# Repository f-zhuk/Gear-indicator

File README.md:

# Gear-indicator
A system to monitor the selected gear for bicycles, for those who do not trust their memory

Headunit - a device to display the current gear
Gearunit - a device to transmit the current position of two cables, doubles as a power supply

### System manifest

The main idea of the system is to minimize interaction with the user, reduce buttons and/or settings to the minimum.

The system is designed for long-term/permanent installation and should require minimal maintenance. All its modules should be waterproof and vandal-resistant.

System retains its settings in the local RAM of the corresponding units, always powered from the Battery/shifter unit. If that battery goes flat, all system parameters are lost, and calibration (or learning) should be performed after turning on. Modules can be disconnected from power independently, so it will affect only the related module parameters. 

### Calibration

Whatever position the shifter was left in, it will be considered a first gear after the cold start. First shift has to be upwards, even an incomplete one, to point the cable’s forward direction. If the Headunit reads values outside of the known range, the current gear indicator will move away, and if the value stays stable for ~2 seconds, the gear count and associated shifter value table will be updated.

To save battery, all modules should go in and out of deep sleep upon Headunit's request. While active, deep sleep should be triggered if no movement is detected for a minute. 
While in a deep sleep, any movement should trigger a deep sleep exit.

With an IMU within the battery module firmly attached to the bicycle frame, it is possible to estimate bike speed.

Braking range can be determined and dynamically expanded on the fly.

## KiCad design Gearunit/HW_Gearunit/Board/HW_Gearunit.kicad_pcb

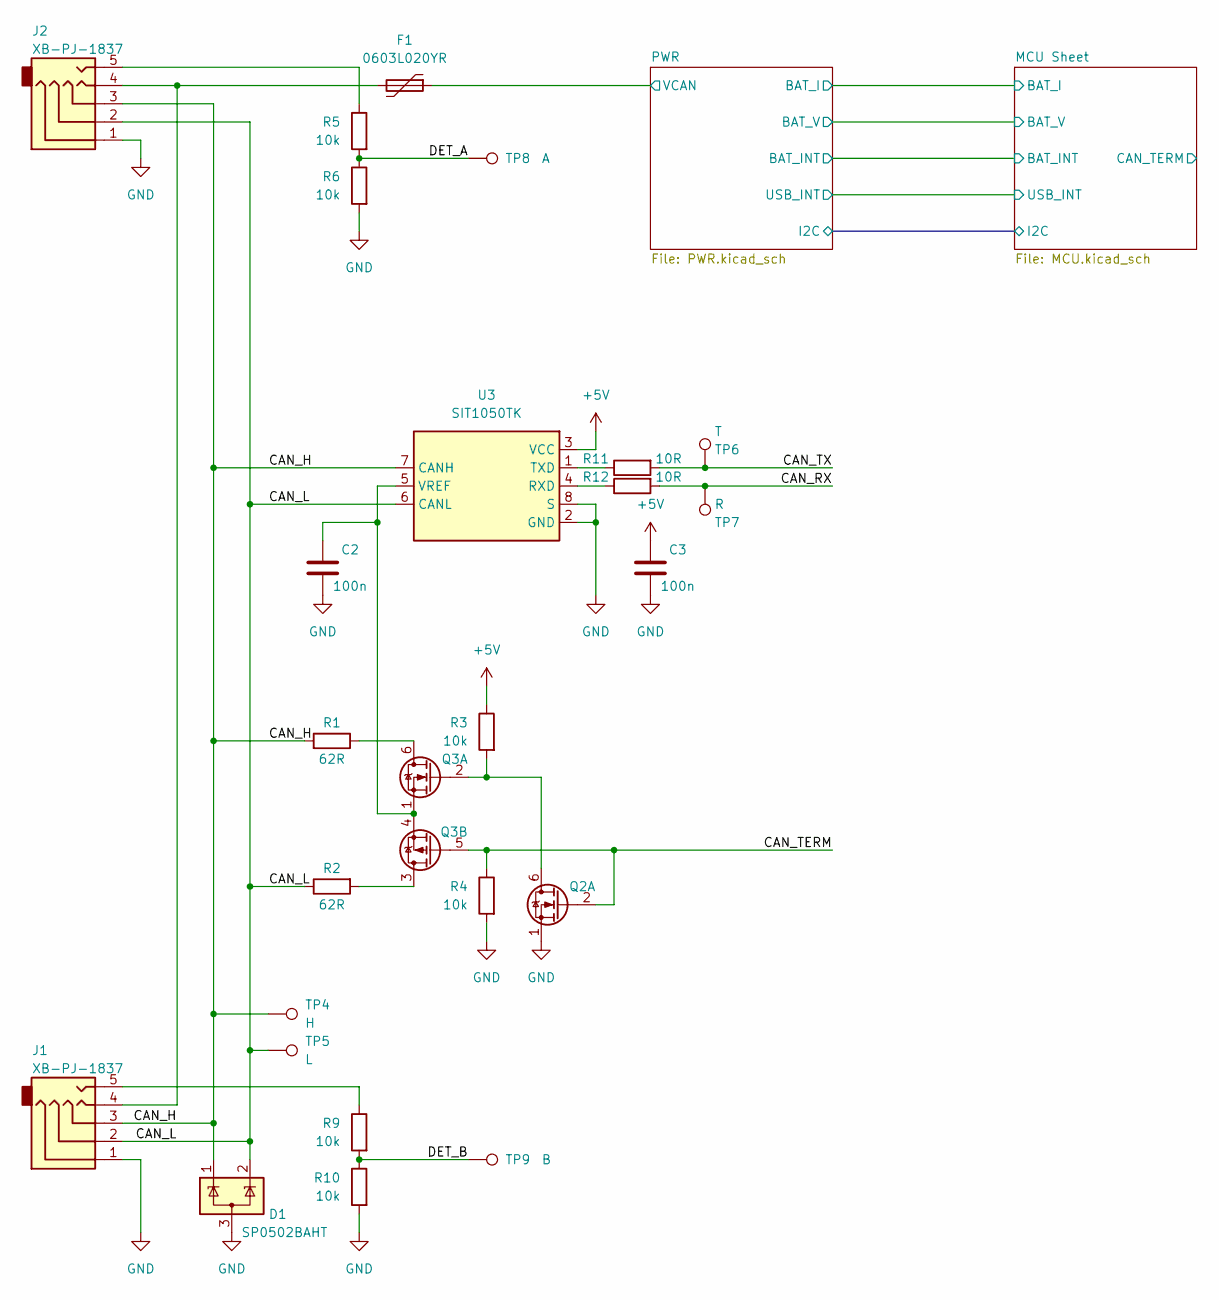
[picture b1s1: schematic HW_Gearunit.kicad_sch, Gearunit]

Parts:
C2, C3: 100n; C_0402_1005Metric; MPN CL05B104KB54PNC
D1: SP0502BAHT; SOT-23; MPN SP0502BAHT
F1: 0603L020YR; Fuse_0603_1608Metric; MPN 0603L020YR
J1, J2: XB-PJ-1837; MPN XB-PJ-1837
Q2, Q3: DMC2400UV; SOT-563; MPN DMC2400UV
R1, R2: 62R; R_0805_2012Metric; MPN RC0805FR-0762RL
R3, R4, R5, R6, R9, R10: 10k; R_0402_1005Metric; MPN 0402WGF1002TCE
R11, R12: 10R; R_0402_1005Metric; MPN 0402WGF100JTCE
TP4: H; TestPoint_Pad_D1.5mm
TP5: L; TestPoint_Pad_D1.5mm
TP6: T; TestPoint_Pad_D1.5mm
TP7: R; TestPoint_Pad_D1.5mm
TP8: A; TestPoint_Pad_D1.5mm
TP9: B; TestPoint_Pad_D1.5mm
U3: SIT1050TK; DFN-8-1EP_3x3mm_P0.65mm_EP1.5x2.25mm; MPN SIT1050TK

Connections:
+5V: C3.2, R3.1, U3.3 (VCC)
/CAN_H: D1.1 (K), J1.3, J2.3, R1.2, TP4.1, U3.7 (CANH)
/CAN_L: D1.2 (K), J1.2, J2.2, R2.1, TP5.1, U3.6 (CANL)
/CAN_RX: R12.2, TP7.1
/CAN_TERM: Q2.2 (G), Q3.5 (G), R4.1
/CAN_TX: R11.2, TP6.1
/DET_A: R5.2, R6.1, TP8.1
/DET_B: R9.2, R10.1, TP9.1
/PWR/VCAN: F1.1; also elsewhere on the board
GND: C2.1, C3.1, D1.3 (A), J1.1, J2.1, Q2.1 (S), R4.2, R6.2, R10.2, U3.2 (GND), U3.8 (S); also elsewhere on the board
unnamed: F1.2, J1.4, J2.4
unnamed: J1.5, R9.1
unnamed: J2.5, R5.1
unnamed: Q2.6 (D), Q3.2 (G), R3.2
unnamed: Q3.6 (D), R1.1
unnamed: C2.2, Q3.1 (S), Q3.4 (S), U3.5 (VREF)
unnamed: Q3.3 (D), R2.2
unnamed: R12.1, U3.4 (RXD)
unnamed: R11.1, U3.1 (TXD)

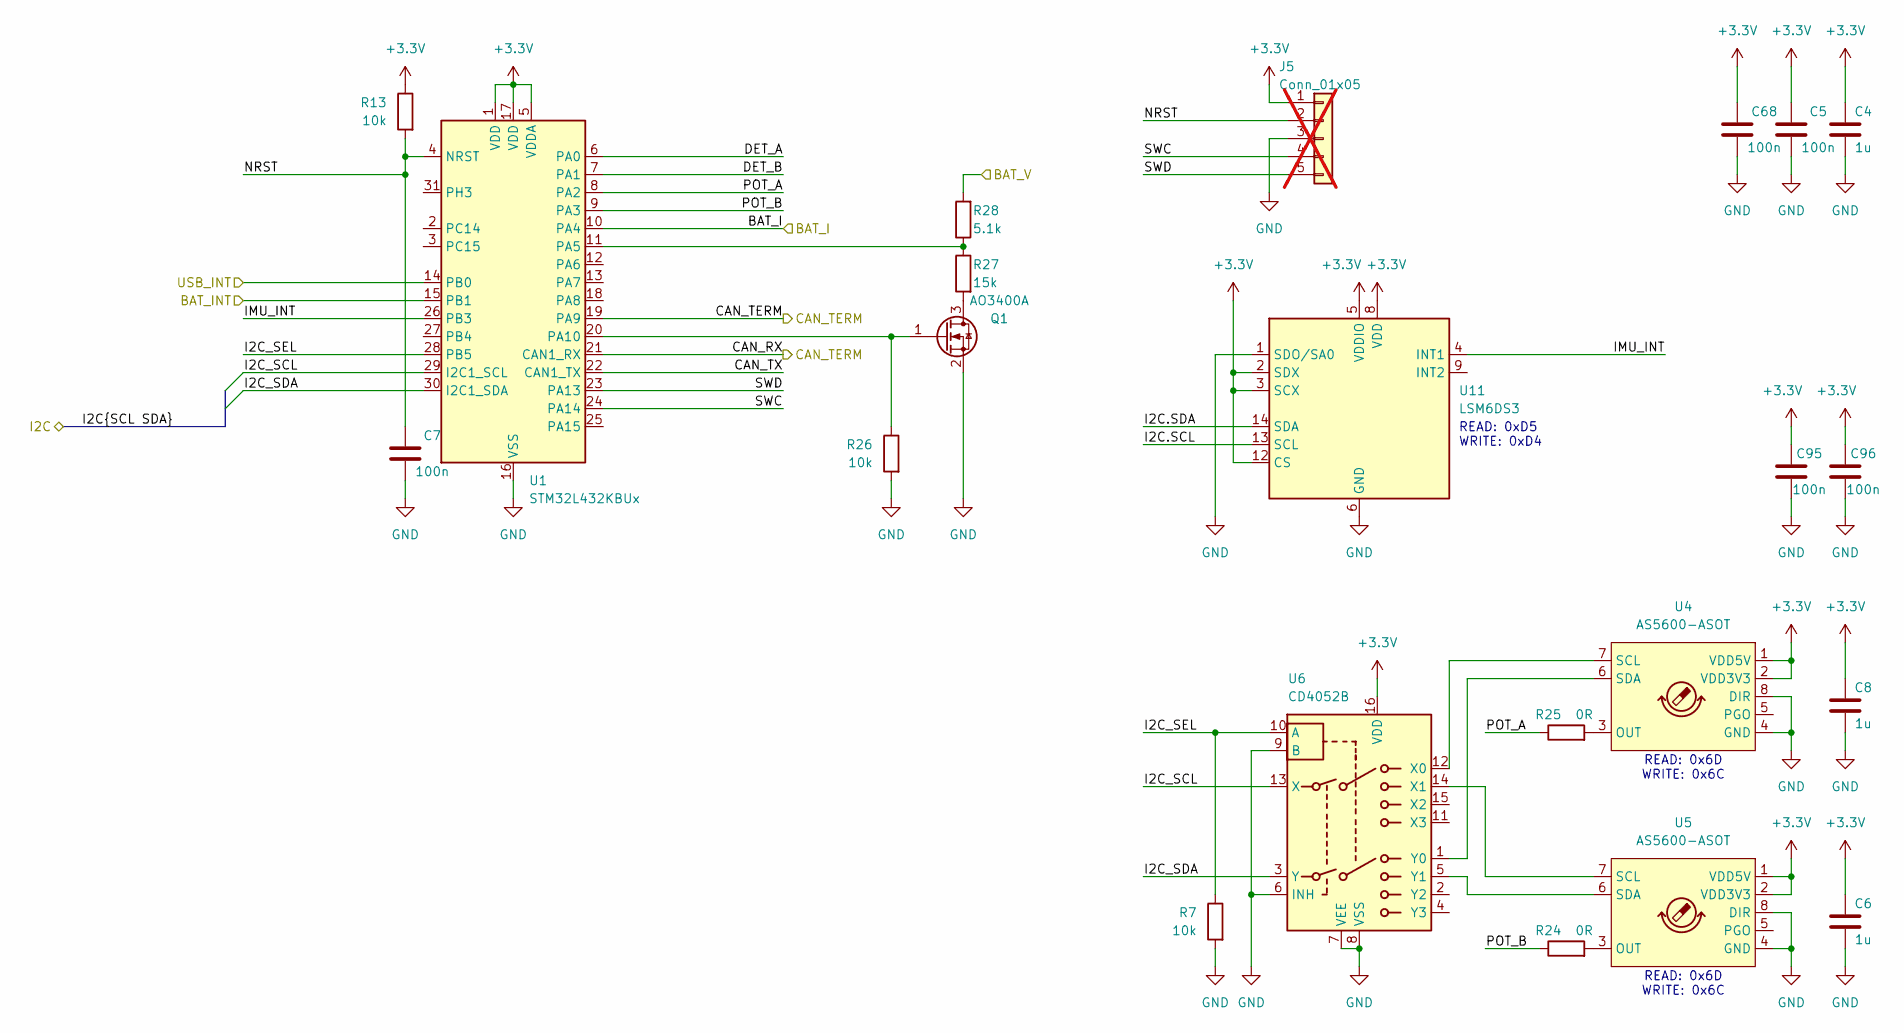
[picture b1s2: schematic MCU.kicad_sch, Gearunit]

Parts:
C4, C6, C8: 1u; C_0603_1608Metric; MPN CL10A105KB8NNNC
C5, C7, C68, C95, C96: 100n; C_0402_1005Metric; MPN CL05B104KB54PNC
J5: Conn_01x05; PinHeader_1x05_P2.54mm_Vertical; not fitted
Q1: AO3400A; SOT-23; MPN AO3400A
R7, R13, R26: 10k; R_0402_1005Metric; MPN 0402WGF1002TCE
R24, R25: 0R; R_0402_1005Metric; MPN 0402WGF0000TCE
R27: 15k; R_0402_1005Metric; MPN 0402WGF1502TCE
R28: 5.1k; R_0402_1005Metric; MPN 0402WGF5101TCE
U1: STM32L432KBUx; QFN-32-1EP_5x5mm_P0.5mm_EP3.45x3.45mm; MPN STM32L432KBU
U4, U5: AS5600-ASOT; SO-8_3.9x4.9mm_P1.27mm; MPN AS5600-ASOT
U6: CD4052B; TSSOP-16_4.4x5mm_P0.65mm
U11: LSM6DS3; LGA-14_3x2.5mm_P0.5mm_LayoutBorder3x4y; MPN LSM6DS3

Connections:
+3.3V: C4.2, C5.2, C6.2, C8.2, C68.2, C95.1, C96.1, J5.1, R13.1, U1.1 (VDD), U1.5 (VDDA), U1.17 (VDD), U4.1 (VDD5V), U4.2 (VDD3V3), U5.1 (VDD5V), U5.2 (VDD3V3), U6.16 (VDD), U11.2 (SDX), U11.3 (SCX), U11.5 (VDDIO), U11.8 (VDD), U11.12 (CS); also elsewhere on the board
/MCU Sheet/BAT_I: U1.10 (PA4); also elsewhere on the board
/MCU Sheet/BAT_INT: U1.15 (PB1); also elsewhere on the board
/MCU Sheet/BAT_V: R28.2; also elsewhere on the board
/MCU Sheet/CAN_RX: U1.19 (PA9), U1.21 (CAN1_RX)
/MCU Sheet/CAN_TX: U1.22 (CAN1_TX)
/MCU Sheet/DET_A: U1.6 (PA0)
/MCU Sheet/DET_B: U1.7 (PA1)
/MCU Sheet/I2C.SCL: U11.13 (SCL); also elsewhere on the board
/MCU Sheet/I2C.SDA: U11.14 (SDA); also elsewhere on the board
/MCU Sheet/I2C_SCL: U1.29 (I2C1_SCL), U6.13 (X)
/MCU Sheet/I2C_SDA: U1.30 (I2C1_SDA), U6.3 (Y)
/MCU Sheet/I2C_SEL: R7.1, U1.28 (PB5), U6.10 (A)
/MCU Sheet/IMU_INT: U1.26 (PB3), U11.4 (INT1)
/MCU Sheet/NRST: C7.2, J5.2, R13.2, U1.4 (NRST)
/MCU Sheet/POT_A: R25.1, U1.8 (PA2)
/MCU Sheet/POT_B: R24.1, U1.9 (PA3)
/MCU Sheet/SWC: J5.4, U1.24 (PA14)
/MCU Sheet/SWD: J5.5, U1.23 (PA13)
/MCU Sheet/USB_INT: U1.14 (PB0); also elsewhere on the board
GND: C4.1, C5.1, C6.1, C7.1, C8.1, C68.1, C95.2, C96.2, J5.3, Q1.2 (S), R7.2, R26.2, U1.16 (VSS), U1.32 (VSS), U1.33 (VSS), U4.4 (GND), U4.8 (DIR), U5.4 (GND), U5.8 (DIR), U6.6 (INH), U6.7 (VEE), U6.8 (VSS), U6.9 (B), U11.1 (SDO/SA0), U11.6 (GND), U11.7 (GND); also elsewhere on the board
unnamed: Q1.3 (D), R27.2
unnamed: Q1.1 (G), R26.1, U1.20 (PA10)
unnamed: R27.1, R28.1, U1.11 (PA5)
unnamed: R25.2, U4.3 (OUT)
unnamed: U4.7 (SCL), U6.12 (X0)
unnamed: U4.6 (SDA), U6.1 (Y0)
unnamed: R24.2, U5.3 (OUT)
unnamed: U5.7 (SCL), U6.14 (X1)
unnamed: U5.6 (SDA), U6.5 (Y1)

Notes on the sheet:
READ: 0x6D WRITE: 0x6C
READ: 0xD5 WRITE: 0xD4

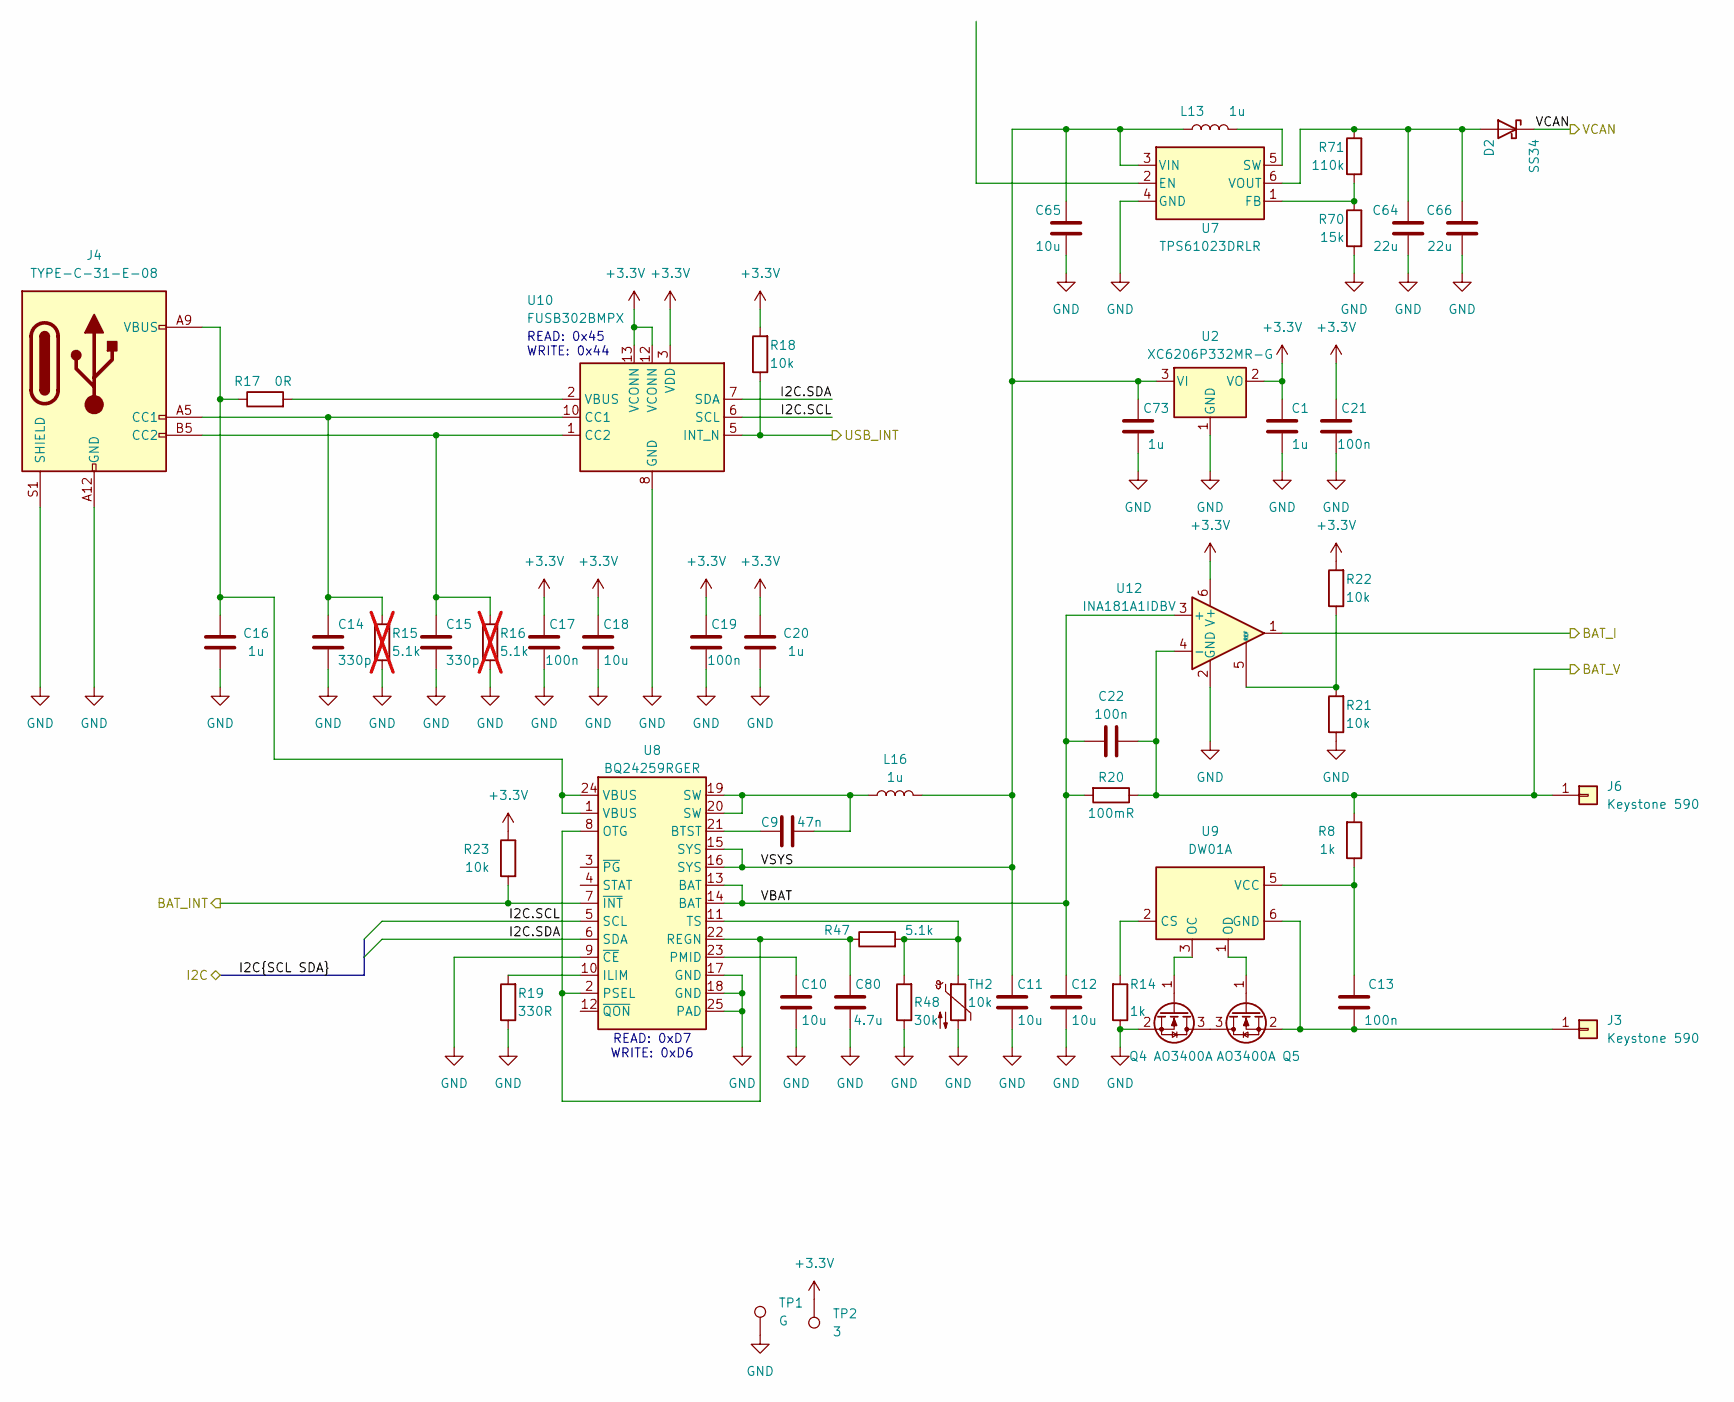
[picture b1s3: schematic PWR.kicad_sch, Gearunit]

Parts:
C1, C16, C20, C73: 1u; C_0603_1608Metric; MPN CL10A105KB8NNNC
C9: 47n; C_0402_1005Metric; MPN GRM155R71E473KA88D
C10, C11, C12, C18, C65: 10u; C_0603_1608Metric; MPN CL10A106MA8NRNC
C13, C17, C19, C21, C22: 100n; C_0402_1005Metric; MPN CL05B104KB54PNC
C14, C15: 330p; C_0402_1005Metric; MPN CL05C331JB5NNNC
C64, C66: 22u; C_0805_2012Metric; MPN CL21A226MAQNNNE
C80: 4.7u; C_0603_1608Metric; MPN CL10A475KO8NNNC
D2: SS34; D_SMA; MPN SS34
J3, J6: Keystone 590; Connector_Keystone_590; MPN 590
J4: TYPE-C-31-E-08; USB_C_Receptacle_HRO_TYPE-C-31-E-08; MPN TYPE-C-31-E-08
L13, L16: 1u; L_Murata_DFE201610P; MPN DFE201610E-1R0M=P2
Q4, Q5: AO3400A; SOT-23; MPN AO3400A
R8, R14: 1k; R_0402_1005Metric; MPN 0402WGF1001TCE
R15, R16: 5.1k; R_0402_1005Metric; MPN 0402WGF5101TCE; not fitted
R17: 0R; R_0402_1005Metric; MPN 0402WGF0000TCE
R18, R21, R22, R23: 10k; R_0402_1005Metric; MPN 0402WGF1002TCE
R19: 330R; R_0402_1005Metric; MPN 0402WGF3300TCE
R20: 100mR; R_0603_1608Metric; MPN ERJ3RSFR10V
R47: 5.1k; R_0402_1005Metric; MPN 0402WGF5101TCE
R48: 30k; R_0603_1608Metric; MPN 0603WAF3002T5E
R70: 15k; R_0402_1005Metric; MPN 0402WGF1502TCE
R71: 110k; R_0603_1608Metric; MPN 0603WAF1103T5E
TH2: 10k; R_0603_1608Metric; MPN SDNT1608X103F3435FTF
TP1: G; TestPoint_Pad_D1.5mm
TP2: 3; TestPoint_Pad_D1.5mm
U2: XC6206P332MR-G; SOT-23-3; MPN XC6206P332MR-G
U7: TPS61023DRLR; SOT-563; MPN TPS61023DRLR
U8: BQ24259RGER; Texas_RGE0024H_VQFN-24-1EP_4x4mm_P0.5mm_EP2.7x2.7mm
U9: DW01A; SOT-23-6
U10: FUSB302BMPX; WQFN-14-1EP_2.5x2.5mm_P0.5mm_EP1.45x1.45mm; MPN FUSB302BMPX
U12: INA181A1IDBV; SOT-23-6; MPN INA181A1IDBV

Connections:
+3.3V: C1.2, C17.1, C18.2, C19.1, C20.2, C21.1, R18.2, R22.2, R23.1, TP2.1, U2.2 (VO), U10.3 (VDD), U10.4 (VDD), U10.12 (VCONN), U10.13 (VCONN), U12.6 (V+); also elsewhere on the board
/MCU Sheet/BAT_I: U12.1; also elsewhere on the board
/MCU Sheet/BAT_INT: R23.2, U8.7 (~INT); also elsewhere on the board
/MCU Sheet/BAT_V: C22.2, J6.1, R8.2, R20.1, U12.4 (-); also elsewhere on the board
/MCU Sheet/I2C.SCL: U8.5 (SCL), U10.6 (SCL); also elsewhere on the board
/MCU Sheet/I2C.SDA: U8.6 (SDA), U10.7 (SDA); also elsewhere on the board
/MCU Sheet/USB_INT: R18.1, U10.5 (INT_N); also elsewhere on the board
/PWR/VBAT: C12.2, C22.1, R20.2, U8.13 (BAT), U8.14 (BAT), U12.3 (+)
/PWR/VCAN: D2.1 (K); also elsewhere on the board
/PWR/VSYS: C11.2, C65.2, C73.2, L13.2, L16.2, U2.3 (VI), U7.3 (VIN), U8.15 (SYS), U8.16 (SYS)
GND: C1.1, C10.1, C11.1, C12.1, C14.1, C15.1, C16.1, C17.2, C18.1, C19.2, C20.1, C21.2, C64.2, C65.1, C66.2, C73.1, C80.1, J4.A12 (GND), J4.B12 (GND), J4.S1 (SHIELD), Q4.2 (S), R14.1, R15.2, R16.2, R19.1, R21.1, R48.1, R70.2, TH2.2, TP1.1, U2.1 (GND), U7.4 (GND), U8.9 (~CE), U8.17 (GND), U8.18 (GND), U8.25 (PAD), U10.8 (GND), U10.9 (GND), U10.15 (GND), U12.2 (GND); also elsewhere on the board
unnamed: C9.2, L16.1, U8.19 (SW), U8.20 (SW)
unnamed: C16.2, J4.A9 (VBUS), J4.B9 (VBUS), R17.1, U8.1 (VBUS), U8.24 (VBUS)
unnamed: C64.1, C66.1, D2.2 (A), R71.1, U7.6 (VOUT)
unnamed: C13.1, J3.1, Q5.2 (S), U9.6 (GND)
unnamed: C14.2, J4.A5 (CC1), R15.1, U10.10 (CC1), U10.11 (CC1)
unnamed: C15.2, J4.B5 (CC2), R16.1, U10.1 (CC2), U10.14 (CC2)
unnamed: Q4.3 (D), Q5.3 (D)
unnamed: Q4.1 (G), U9.3 (OC)
unnamed: Q5.1 (G), U9.1 (OD)
unnamed: R70.1, R71.2, U7.1 (FB)
unnamed: L13.1, U7.5 (SW)
unnamed: C9.1, U8.21 (BTST)
unnamed: R19.2, U8.10 (ILIM)
unnamed: C80.2, R47.1, U8.2 (PSEL), U8.8 (OTG), U8.22 (REGN)
unnamed: C10.2, U8.23 (PMID)
unnamed: R47.2, R48.2, TH2.1, U8.11 (TS)
unnamed: R14.2, U9.2 (CS)
unnamed: C13.2, R8.1, U9.5 (VCC)
unnamed: R17.2, U10.2 (VBUS)
unnamed: R21.2, R22.1, U12.5 (REF)

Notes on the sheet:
READ: 0x45 WRITE: 0x44
READ: 0xD7 WRITE: 0xD6

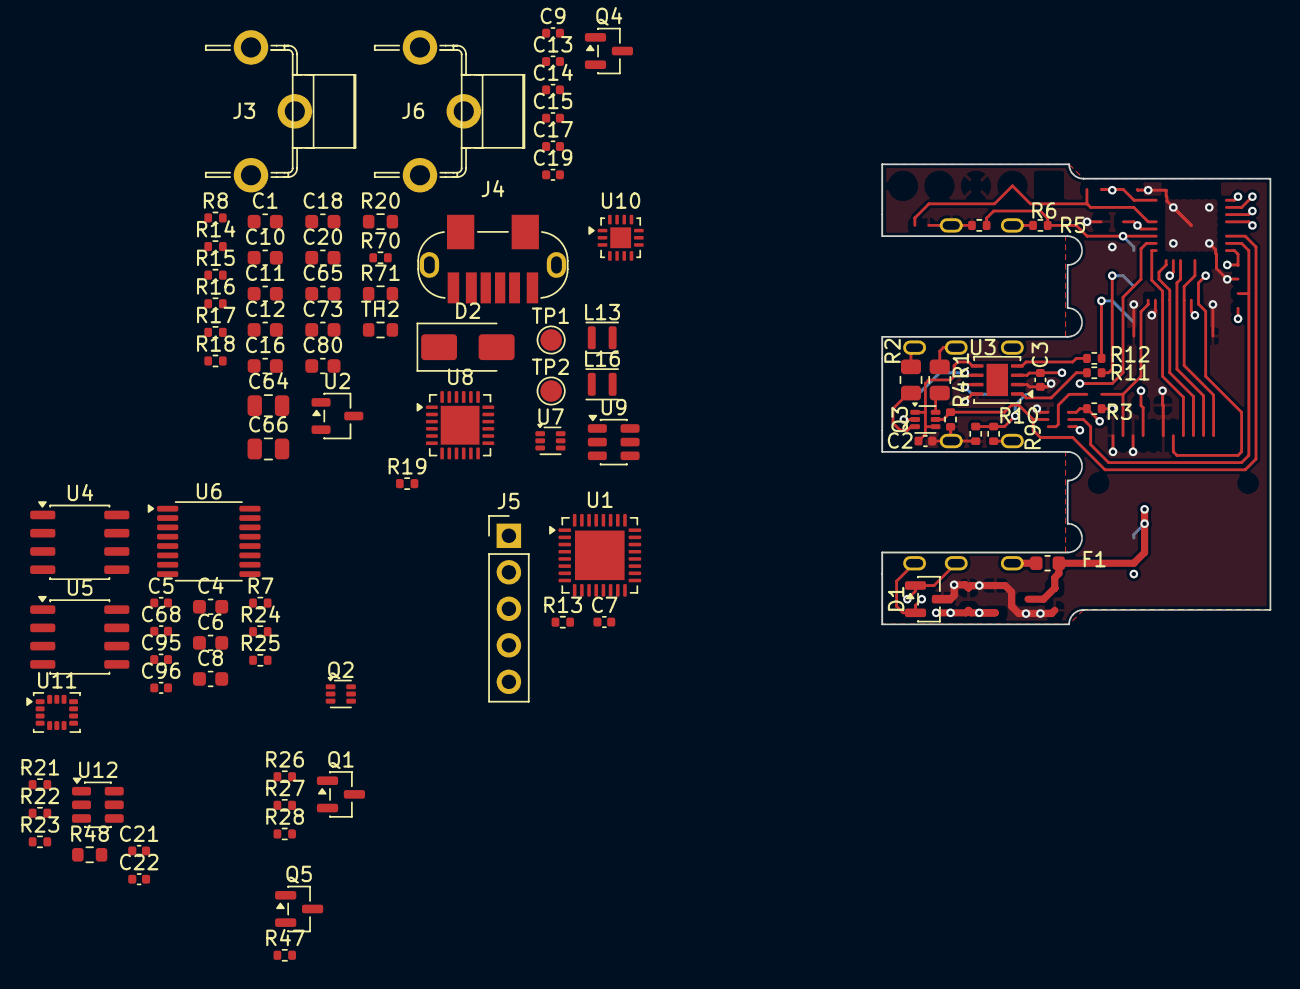
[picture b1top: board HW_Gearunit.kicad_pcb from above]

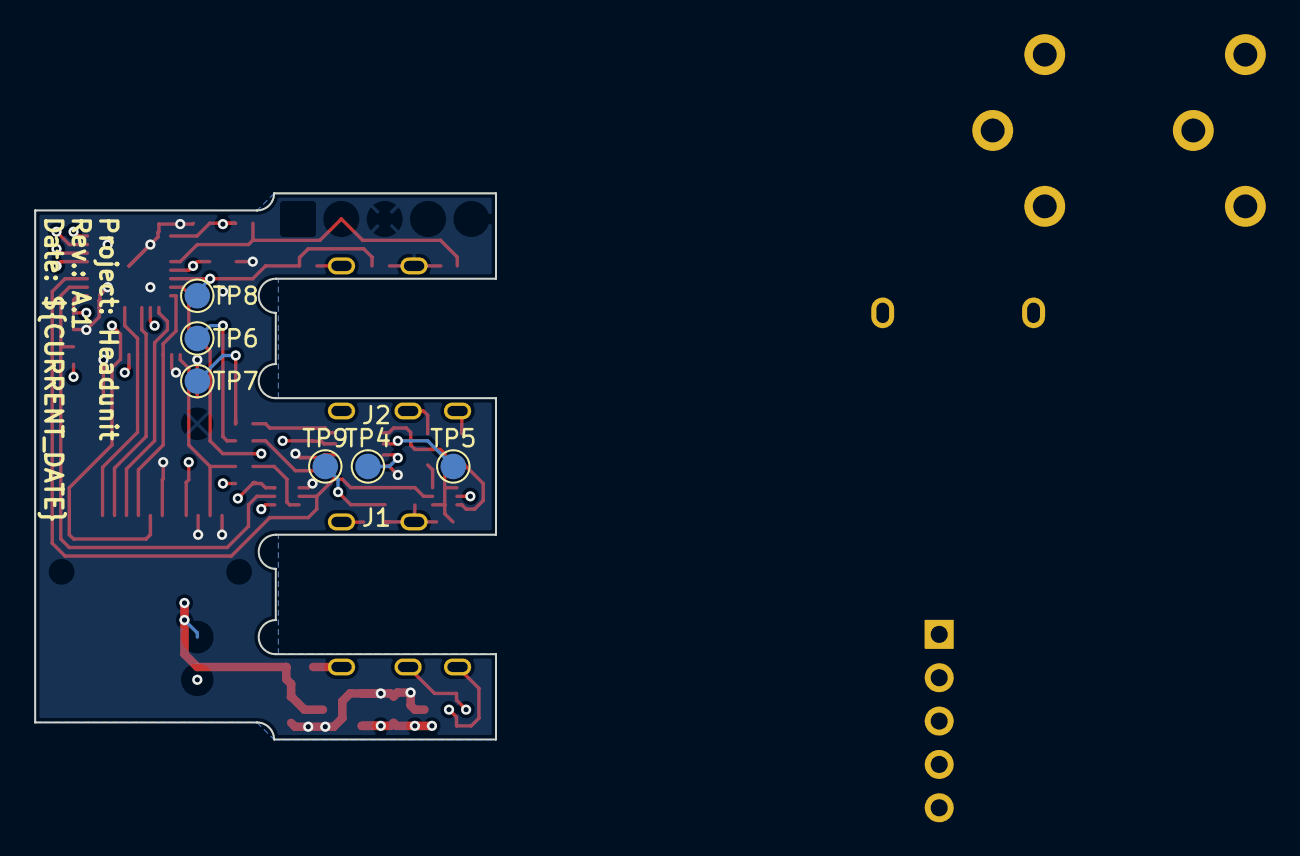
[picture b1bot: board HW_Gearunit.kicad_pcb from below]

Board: 4 copper layers, 27.0 x 32.0 mm, 99 parts (8 on the bottom side), 67 nets.

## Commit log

2026-01-24 LVGL addition started
2026-01-25 LVGL use attempt - too large to fit
2026-01-25 Added minimalistic display library
2026-01-26 Adapting code for use with HAL
2026-01-26 Integrated displayInit()
2026-01-26 Now compilable and ready for display init debug
2026-01-26 LCD initialized, data transmission tests
2026-01-28 Found memory to matrix mapping
2026-01-28 Display test pattern fill
2026-01-28 Framebuffer 40*80 at 4bit depth added. Pallet test
2026-01-29 Fixed garbage on startup, tested character output concept
2026-01-29 Renamed directories, adding fonts
2026-01-30 Fonts added
2026-02-01 Started case 3D model
2026-02-02 KiCAD project created
2026-02-02 Rectangle fill and boundary checks added
2026-02-02 Fixed issue with putchar() occasional artifacts
2026-02-03 Headunit case model general vision created
2026-02-03 PCB shape improved
2026-02-03 Added canopennode submodule
2026-02-06 Added Canopen node submodule and added timer for timebase
2026-02-07 Initially integrated CanOpenNode_STM32 into the application
2026-02-07 Derived Gearunit from Headunit
2026-02-12 Configured transmit PDO for the Gearunit
2026-02-12 Stable PDO transmission, but does not work on CH32F because the second ADC is missing
2026-02-13 Adapted Gearunit firmware for WCH CH32F103C8
2026-02-13 Doubled screen resolution
2026-03-15 Attempted to add headunit RPDO
2026-03-15 Basic RPDO implemented for Headunit, display corruption fixed
2026-03-16 Started adding gear learn logic
2026-03-17 Started implementing pallete and partial redraw feature, discovered a color corruption bug
2026-03-18 Fixed colour bug.
2026-03-19 Partial redraw done. Started adding new fonts
2026-03-19 Added 40pt font and font selection option
2026-03-20 Added unscii pixel-perfect font with color support and null-terminated string output
2026-03-20 Basic number-string conversion, shifter logic improvements
2026-03-20 Fixes in shifter gear detection algorithm
2026-03-21 Implemented main logic
2026-03-21 Debug information hidden for better performance
2026-03-23 Exported fabrication files
2026-03-27 Gearunit update
2026-03-30 Gearunit updates, Readme updated
2026-03-30 Renders added, readme updated
